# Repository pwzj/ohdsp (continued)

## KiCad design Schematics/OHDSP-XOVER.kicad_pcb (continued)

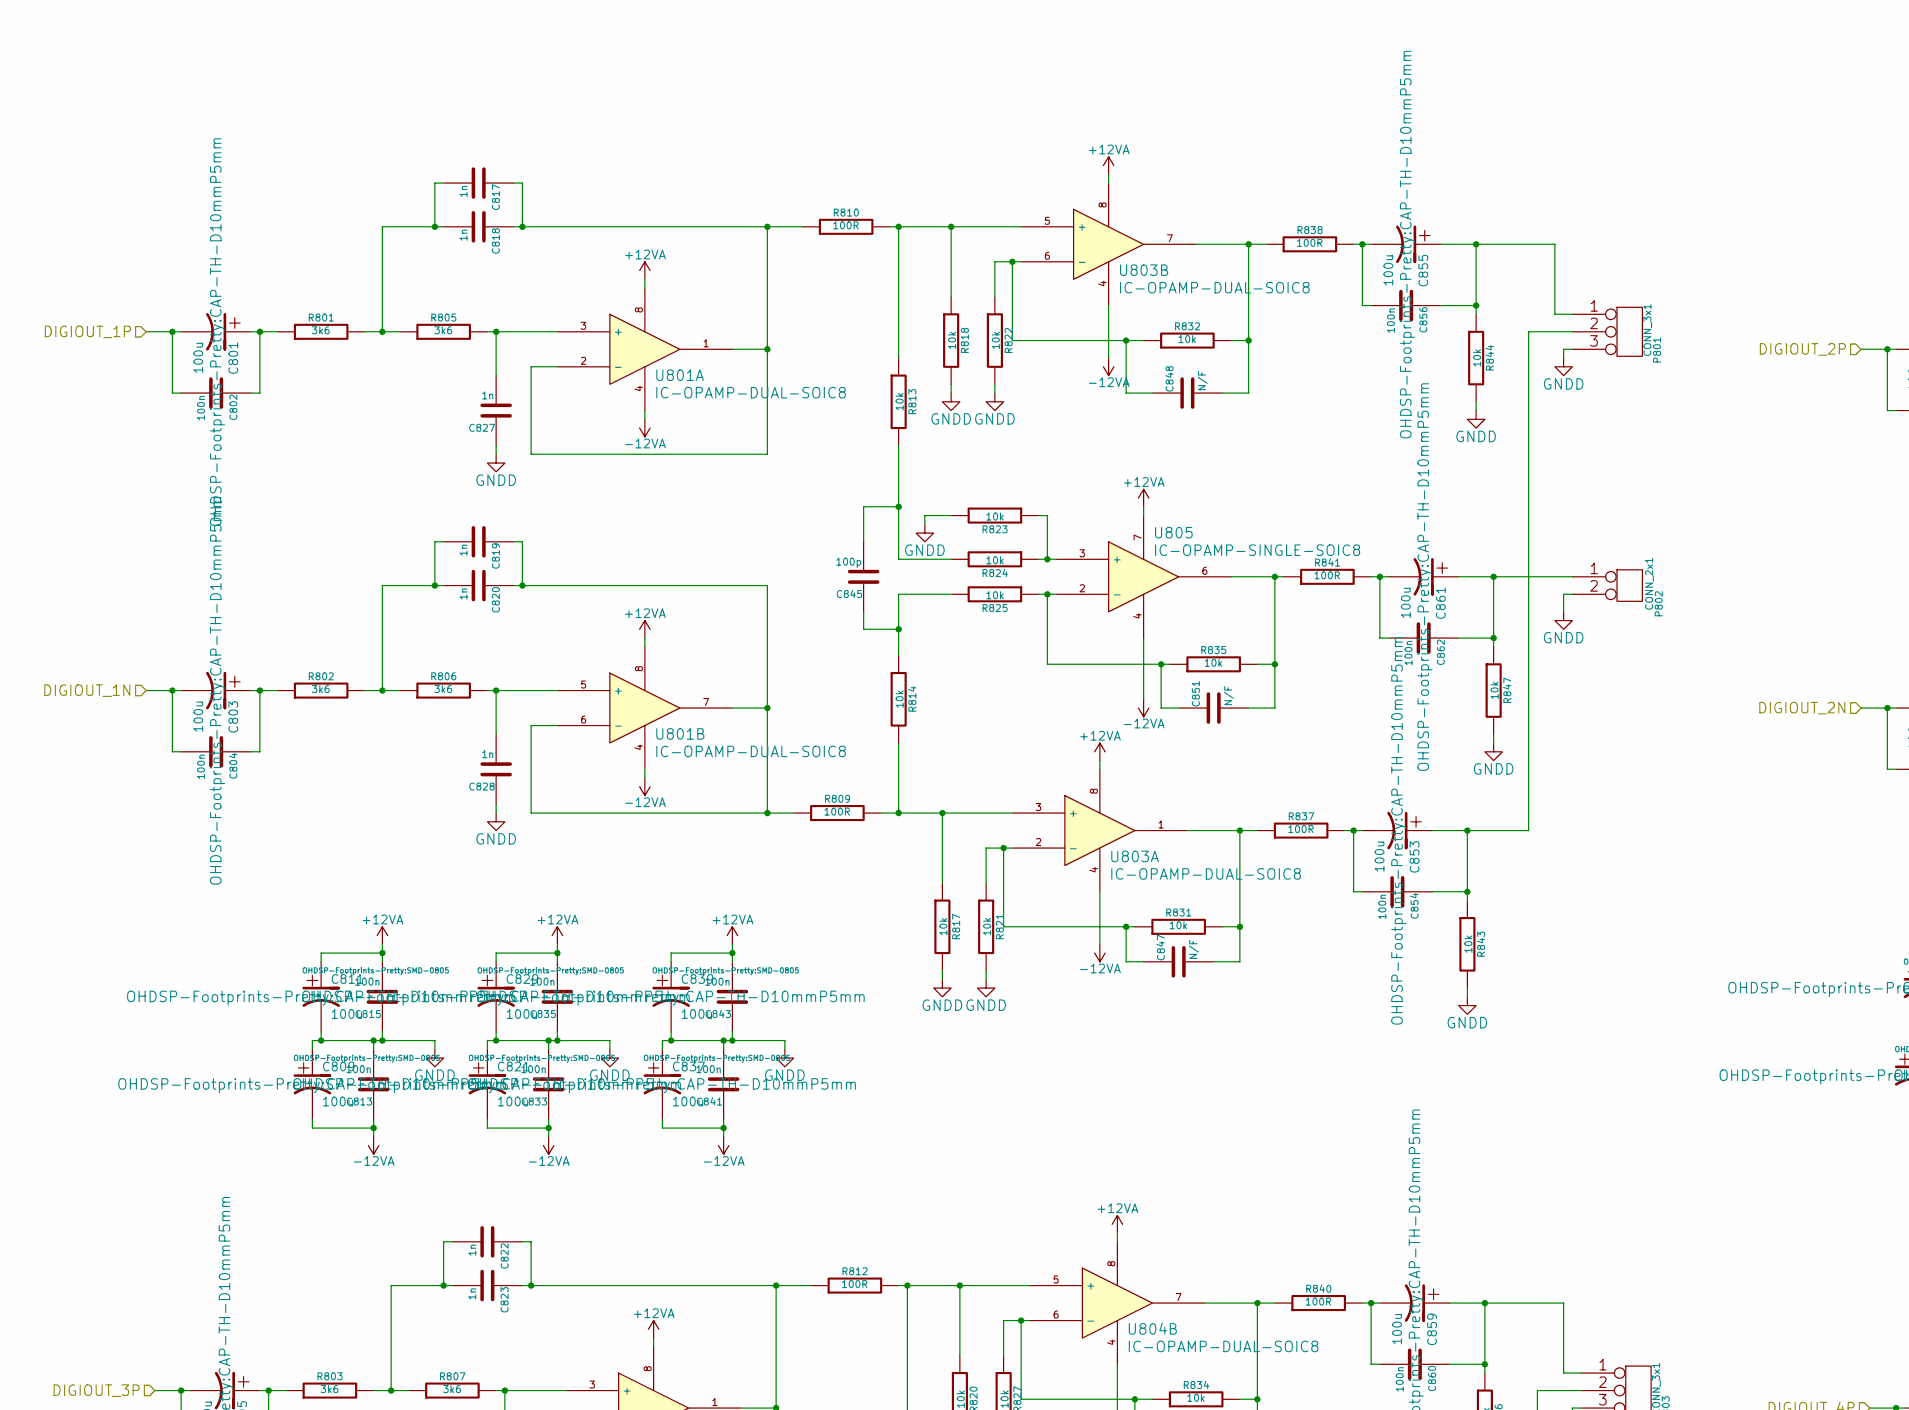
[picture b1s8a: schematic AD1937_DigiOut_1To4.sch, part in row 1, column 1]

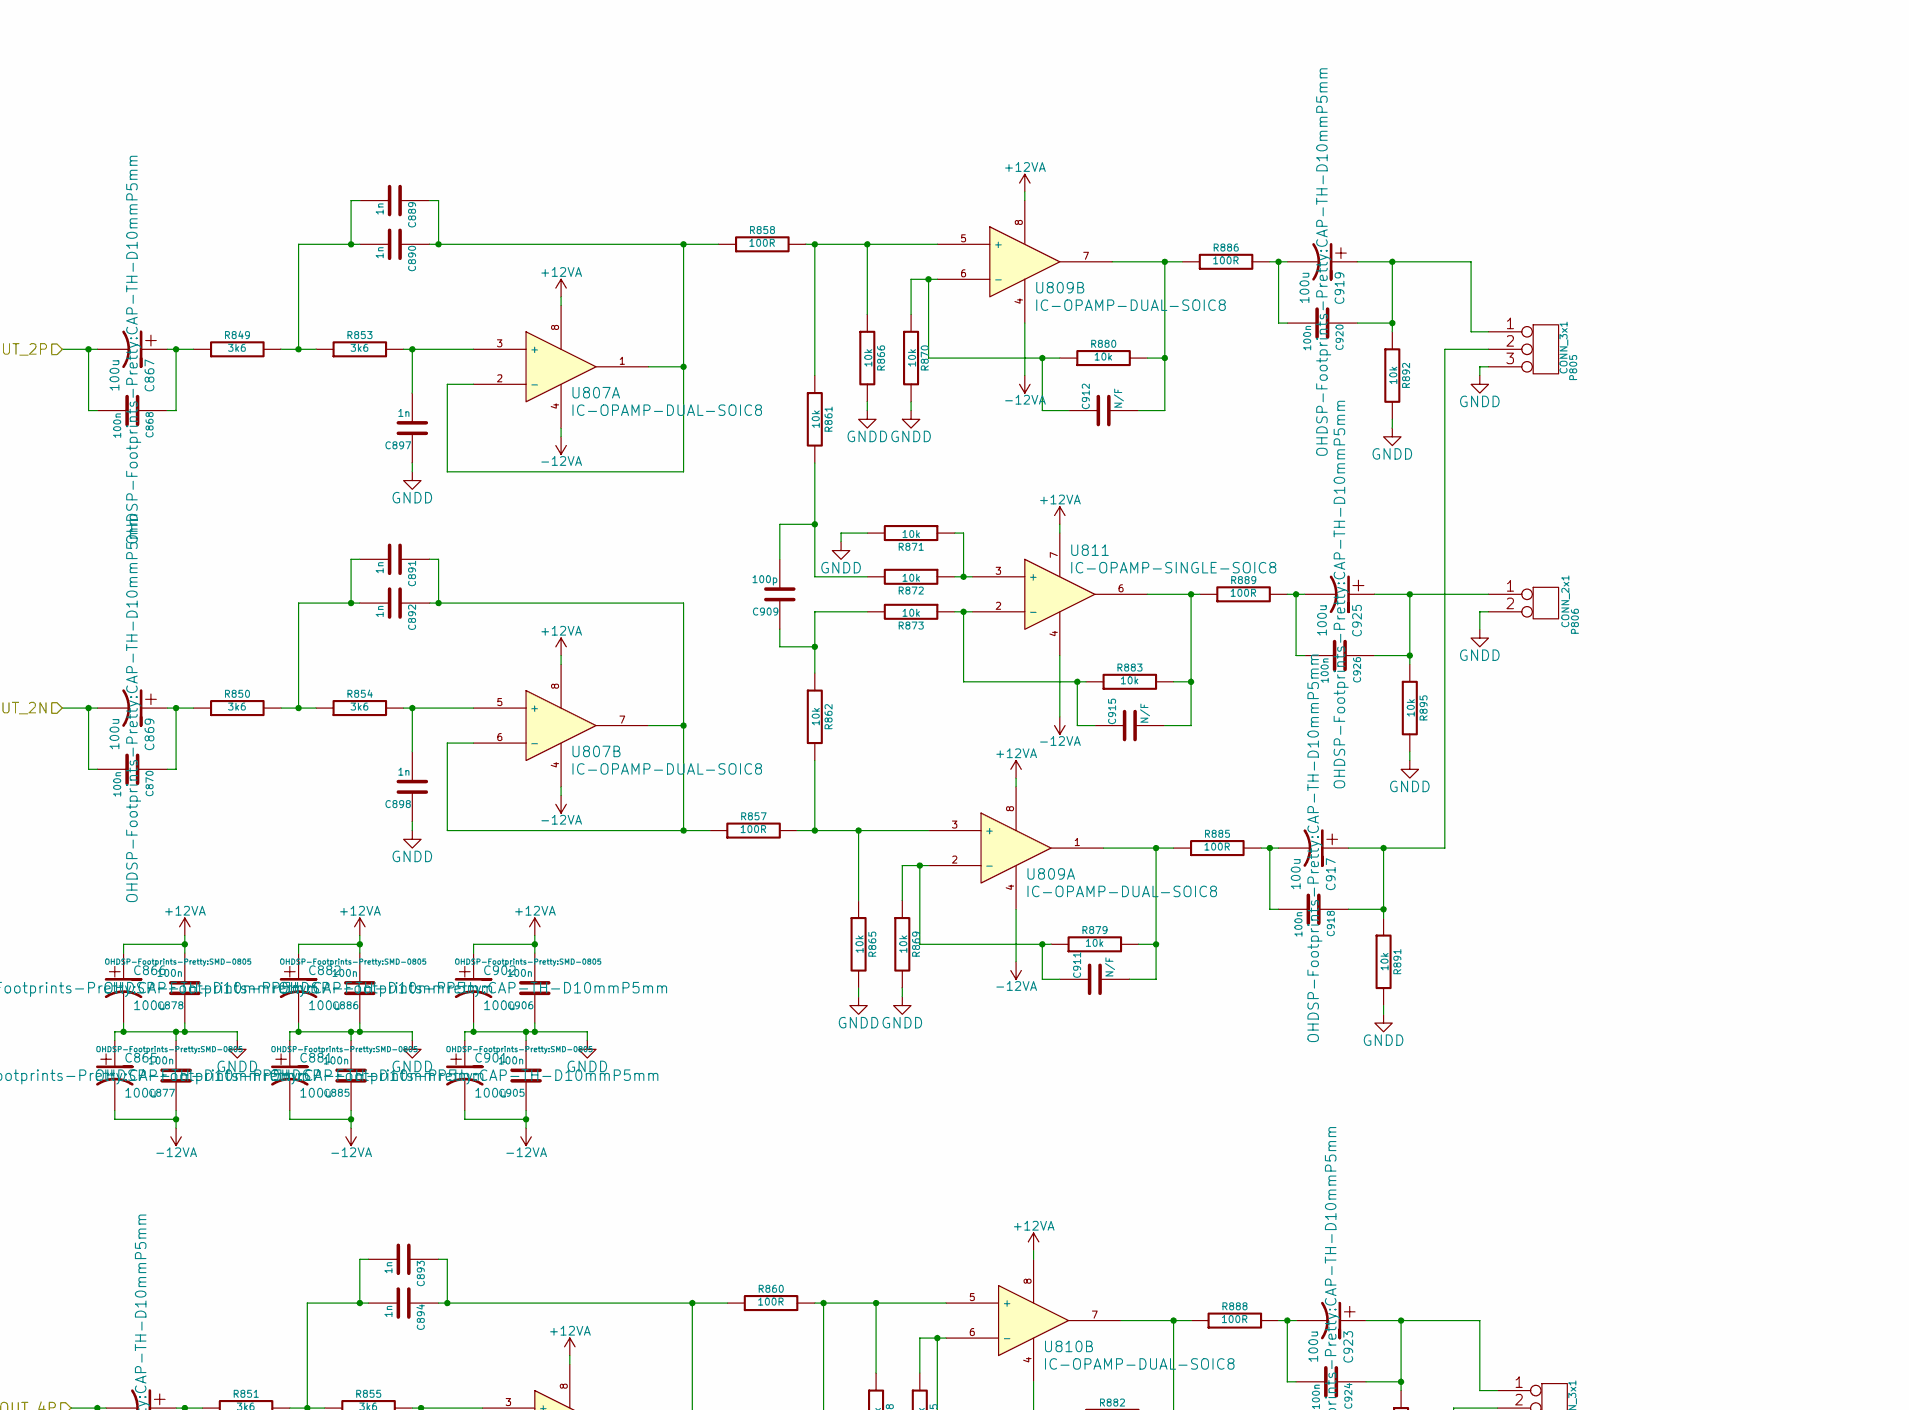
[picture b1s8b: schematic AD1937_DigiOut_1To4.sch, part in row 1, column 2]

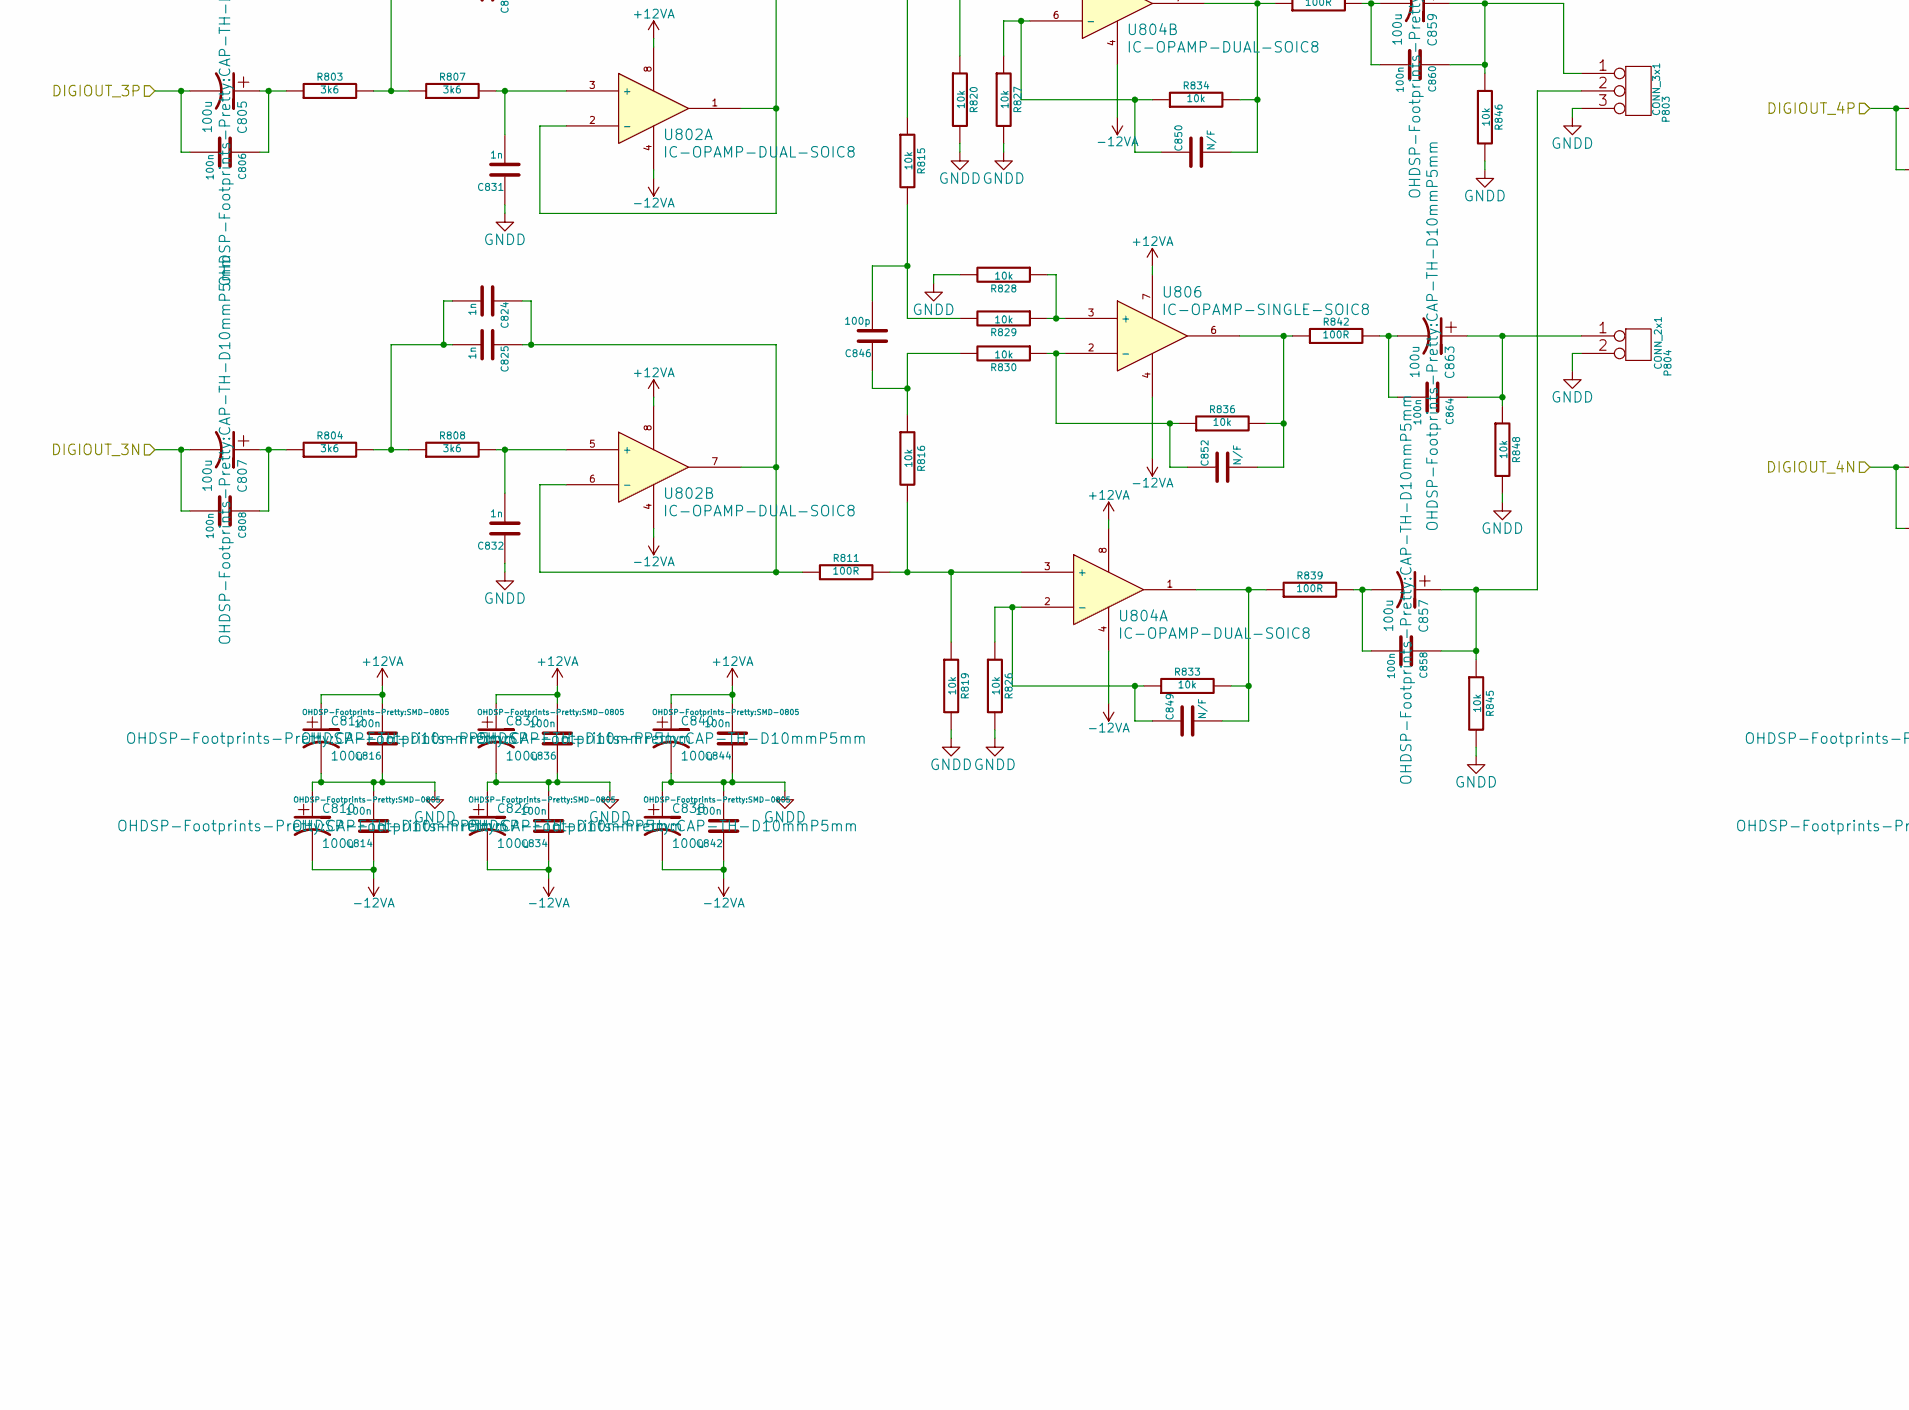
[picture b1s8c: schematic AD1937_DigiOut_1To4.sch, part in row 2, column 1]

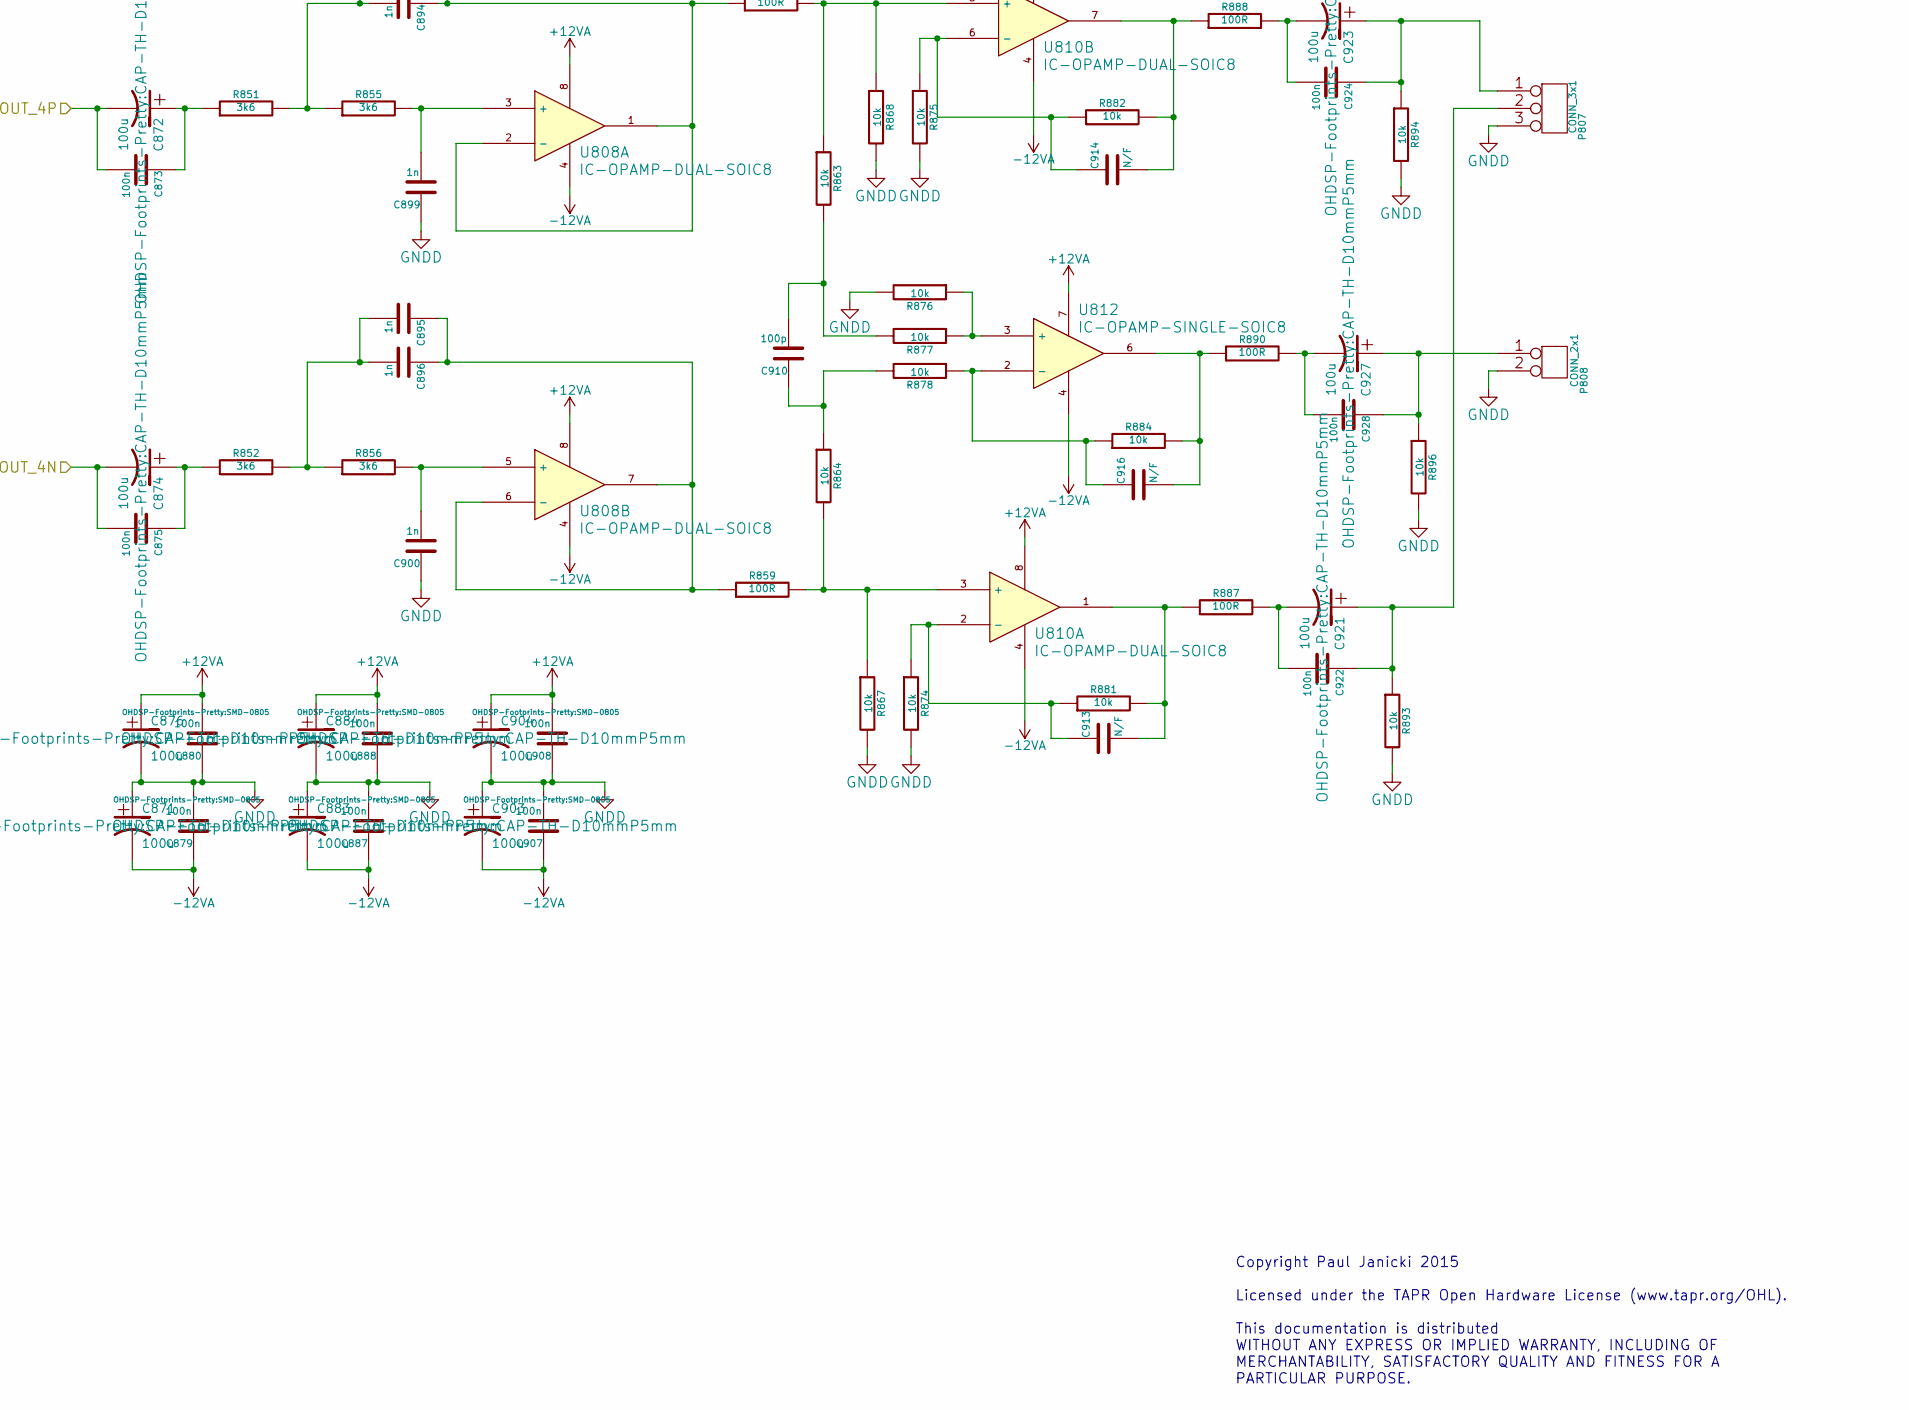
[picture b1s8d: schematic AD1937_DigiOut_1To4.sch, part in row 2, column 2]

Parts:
C801, C803, C805, C807, C809, C810, C811, C812, C821, C826, C829, C830, C837, C838, C839, C840, C853, C855, C857, C859, C861, C863, C865, C866, C867, C869, C871, C872, C874, C876, C881, C882, C883, C884, C901, C902, C903, C904, C917, C919, C921, C923, C925, C927: 100u; CAP-TH-D10mmP5mm
C802, C804, C806, C808, C854, C856, C858, C860, C862, C864, C868, C870, C873, C875, C918, C920, C922, C924, C926, C928: 100n; CAP_TH_5mm
C813, C814, C815, C816, C833, C834, C835, C836, C841, C842, C843, C844, C877, C878, C879, C880, C885, C886, C887, C888, C905, C906, C907, C908: 100n; SMD-0805
C817, C818, C819, C820, C822, C823, C824, C825, C827, C828, C831, C832, C889, C890, C891, C892, C893, C894, C895, C896, C897, C898, C899, C900: 1n; CAP_TH_5mm
C845, C846, C909, C910: 100p; CAP_TH_5mm
C847, C848, C849, C850, C851, C852, C911, C912, C913, C914, C915, C916: N/F; CAP_TH_5mm
P801, P803, P805, P807: CONN_3x1; CONN_SIL_3
P802, P804, P806, P808: CONN_2x1; CONN_SIL_2
R801, R802, R803, R804, R805, R806, R807, R808, R849, R850, R851, R852, R853, R854, R855, R856: 3k6; TH-RES-0W25
R809, R810, R811, R812, R837, R838, R839, R840, R841, R842, R857, R858, R859, R860, R885, R886, R887, R888, R889, R890: 100R; TH-RES-0W25
R813, R814, R815, R816, R817, R818, R819, R820, R821, R822, R823, R824, R825, R826, R827, R828, R829, R830, R831, R832, R833, R834, R835, R836, R843, R844, R845, R846, R847, R848, R861, R862, R863, R864, R865, R866, R867, R868, R869, R870, R871, R872, R873, R874, R875, R876, R877, R878, R879, R880, R881, R882, R883, R884, R891, R892, R893, R894, R895, R896: 10k; TH-RES-0W25
U801, U802, U803, U804, U807, U808, U809, U810: IC-OPAMP-DUAL-SOIC8; IC_DIP_8
U805, U806, U811, U812: IC-OPAMP-SINGLE-SOIC8; IC_DIP_8

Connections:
+12VA: C811.1, C812.1, C815.2, C816.2, C829.1, C830.1, C835.2, C836.2, C839.1, C840.1, C843.2, C844.2, C866.1, C876.1, C878.2, C880.2, C882.1, C884.1, C886.2, C888.2, C902.1, C904.1, C906.2, C908.2, U801.8, U802.8, U803.8, U804.8, U805.7, U806.7, U807.8, U808.8, U809.8, U810.8, U811.7, U812.7; also elsewhere on the board
-12VA: C809.2, C810.2, C813.1, C814.1, C821.2, C826.2, C833.1, C834.1, C837.2, C838.2, C841.1, C842.1, C865.2, C871.2, C877.1, C879.1, C881.2, C883.2, C885.1, C887.1, C901.2, C903.2, C905.1, C907.1, U801.4, U802.4, U803.4, U804.4, U805.4, U806.4, U807.4, U808.4, U809.4, U810.4, U811.4, U812.4; also elsewhere on the board
/AD1937 CODEC/DAC_OUT1_LN: C803.2, C804.2; also elsewhere on the board
/AD1937 CODEC/DAC_OUT1_LP: C801.2, C802.2; also elsewhere on the board
/AD1937 CODEC/DAC_OUT1_RN: C869.2, C870.2; also elsewhere on the board
/AD1937 CODEC/DAC_OUT1_RP: C867.2, C868.2; also elsewhere on the board
/AD1937 CODEC/DAC_OUT2_LN: C807.2, C808.2; also elsewhere on the board
/AD1937 CODEC/DAC_OUT2_LP: C805.2, C806.2; also elsewhere on the board
/AD1937 CODEC/DAC_OUT2_RN: C874.2, C875.2; also elsewhere on the board
/AD1937 CODEC/DAC_OUT2_RP: C872.2, C873.2; also elsewhere on the board
GNDD: C809.1, C810.1, C811.2, C812.2, C813.2, C814.2, C815.1, C816.1, C821.1, C826.1, C827.1, C828.1, C829.2, C830.2, C831.1, C832.1, C833.2, C834.2, C835.1, C836.1, C837.1, C838.1, C839.2, C840.2, C841.2, C842.2, C843.1, C844.1, C865.1, C866.2, C871.1, C876.2, C877.2, C878.1, C879.2, C880.1, C881.1, C882.2, C883.1, C884.2, C885.2, C886.1, C887.2, C888.1, C897.1, C898.1, C899.1, C900.1, C901.1, C902.2, C903.1, C904.2, C905.2, C906.1, C907.2, C908.1, P801.3, P802.2, P803.3, P804.2, P805.3, P806.2, P807.3, P808.2, R817.2, R818.2, R819.2, R820.2, R821.2, R822.2, R823.2, R826.2, R827.2, R828.2, R843.2, R844.2, R845.2, R846.2, R847.2, R848.2, R865.2, R866.2, R867.2, R868.2, R869.2, R870.2, R871.2, R874.2, R875.2, R876.2, R891.2, R892.2, R893.2, R894.2, R895.2, R896.2; also elsewhere on the board
unnamed: C801.1, C802.1, R801.1
unnamed: C803.1, C804.1, R802.1
unnamed: C805.1, C806.1, R803.1
unnamed: C807.1, C808.1, R804.1
unnamed: C817.1, C818.1, R810.1, U801.1, U801.2 (-)
unnamed: C817.2, C818.2, R801.2, R805.1
unnamed: C819.1, C820.1, R809.1, U801.6 (-), U801.7
unnamed: C819.2, C820.2, R802.2, R806.1
unnamed: C822.1, C823.1, R812.1, U802.1, U802.2 (-)
unnamed: C822.2, C823.2, R803.2, R807.1
unnamed: C824.1, C825.1, R811.1, U802.6 (-), U802.7
unnamed: C824.2, C825.2, R804.2, R808.1
unnamed: C827.2, R805.2, U801.3 (+)
unnamed: C828.2, R806.2, U801.5 (+)
unnamed: C831.2, R807.2, U802.3 (+)
unnamed: C832.2, R808.2, U802.5 (+)
unnamed: C845.1, R814.1, R825.2
unnamed: C845.2, R813.2, R824.2
unnamed: C846.1, R816.1, R830.2
unnamed: C846.2, R815.2, R829.2
unnamed: C847.1, R821.1, R831.1, U803.2 (-)
unnamed: C847.2, R831.2, R837.1, U803.1
unnamed: C848.1, R822.1, R832.1, U803.6 (-)
unnamed: C848.2, R832.2, R838.1, U803.7
unnamed: C849.1, R826.1, R833.1, U804.2 (-)
unnamed: C849.2, R833.2, R839.1, U804.1
unnamed: C850.1, R827.1, R834.1, U804.6 (-)
unnamed: C850.2, R834.2, R840.1, U804.7
unnamed: C851.1, R825.1, R835.1, U805.2 (-)
unnamed: C851.2, R835.2, R841.1, U805.6
unnamed: C852.1, R830.1, R836.1, U806.2 (-)
unnamed: C852.2, R836.2, R842.1, U806.6
unnamed: C853.1, C854.1, P801.2, R843.1
unnamed: C853.2, C854.2, R837.2
unnamed: C855.1, C856.1, P801.1, R844.1
unnamed: C855.2, C856.2, R838.2
unnamed: C857.1, C858.1, P803.2, R845.1
unnamed: C857.2, C858.2, R839.2
unnamed: C859.1, C860.1, P803.1, R846.1
unnamed: C859.2, C860.2, R840.2
unnamed: C861.1, C862.1, P802.1, R847.1
unnamed: C861.2, C862.2, R841.2
unnamed: C863.1, C864.1, P804.1, R848.1
unnamed: C863.2, C864.2, R842.2
unnamed: C867.1, C868.1, R849.1
unnamed: C869.1, C870.1, R850.1
unnamed: C872.1, C873.1, R851.1
unnamed: C874.1, C875.1, R852.1
unnamed: C889.1, C890.1, R858.1, U807.1, U807.2 (-)
unnamed: C889.2, C890.2, R849.2, R853.1
unnamed: C891.1, C892.1, R857.1, U807.6 (-), U807.7
unnamed: C891.2, C892.2, R850.2, R854.1
unnamed: C893.1, C894.1, R860.1, U808.1, U808.2 (-)
unnamed: C893.2, C894.2, R851.2, R855.1
unnamed: C895.1, C896.1, R859.1, U808.6 (-), U808.7
unnamed: C895.2, C896.2, R852.2, R856.1
unnamed: C897.2, R853.2, U807.3 (+)
unnamed: C898.2, R854.2, U807.5 (+)
unnamed: C899.2, R855.2, U808.3 (+)
unnamed: C900.2, R856.2, U808.5 (+)
unnamed: C909.1, R862.1, R873.2
unnamed: C909.2, R861.2, R872.2
unnamed: C910.1, R864.1, R878.2
unnamed: C910.2, R863.2, R877.2
unnamed: C911.1, R869.1, R879.1, U809.2 (-)
unnamed: C911.2, R879.2, R885.1, U809.1
unnamed: C912.1, R870.1, R880.1, U809.6 (-)
unnamed: C912.2, R880.2, R886.1, U809.7
unnamed: C913.1, R874.1, R881.1, U810.2 (-)
unnamed: C913.2, R881.2, R887.1, U810.1
unnamed: C914.1, R875.1, R882.1, U810.6 (-)
unnamed: C914.2, R882.2, R888.1, U810.7
unnamed: C915.1, R873.1, R883.1, U811.2 (-)
unnamed: C915.2, R883.2, R889.1, U811.6
unnamed: C916.1, R878.1, R884.1, U812.2 (-)
unnamed: C916.2, R884.2, R890.1, U812.6
unnamed: C917.1, C918.1, P805.2, R891.1
unnamed: C917.2, C918.2, R885.2
unnamed: C919.1, C920.1, P805.1, R892.1
unnamed: C919.2, C920.2, R886.2
unnamed: C921.1, C922.1, P807.2, R893.1
unnamed: C921.2, C922.2, R887.2
unnamed: C923.1, C924.1, P807.1, R894.1
unnamed: C923.2, C924.2, R888.2
unnamed: C925.1, C926.1, P806.1, R895.1
unnamed: C925.2, C926.2, R889.2
unnamed: C927.1, C928.1, P808.1, R896.1
unnamed: C927.2, C928.2, R890.2
unnamed: R809.2, R814.2, R817.1, U803.3 (+)
unnamed: R810.2, R813.1, R818.1, U803.5 (+)
unnamed: R811.2, R816.2, R819.1, U804.3 (+)
unnamed: R812.2, R815.1, R820.1, U804.5 (+)
unnamed: R823.1, R824.1, U805.3 (+)
unnamed: R828.1, R829.1, U806.3 (+)
unnamed: R857.2, R862.2, R865.1, U809.3 (+)
unnamed: R858.2, R861.1, R866.1, U809.5 (+)
unnamed: R859.2, R864.2, R867.1, U810.3 (+)
unnamed: R860.2, R863.1, R868.1, U810.5 (+)
unnamed: R871.1, R872.1, U811.3 (+)
unnamed: R876.1, R877.1, U812.3 (+)

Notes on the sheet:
Copyright Paul Janicki 2015 Licensed under the TAPR Open Hardware License (www.tapr.org/OHL). This documentation is distributed WITHOUT ANY EXPRESS OR IMPLIED WARRANTY, INCLUDING OF MERCHANTABILITY, SATISFACTORY QUALITY AND FITNESS FOR A PARTICULAR PURPOSE.

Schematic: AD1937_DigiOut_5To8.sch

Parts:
C929, C931, C933, C935, C937, C938, C939, C940, C949, C954, C957, C958, C965, C966, C967, C968, C981, C983, C985, C987, C989, C991, C993, C994, C995, C997, C999, C1000, C1002, C1004, C1009, C1010, C1011, C1012, C1029, C1030, C1031, C1032, C1045, C1047, C1049, C1051, C1053, C1055: 100u; CAP-TH-D10mmP5mm
C930, C932, C934, C936, C982, C984, C986, C988, C990, C992, C996, C998, C1001, C1003, C1046, C1048, C1050, C1052, C1054, C1056: 100n; CAP_TH_5mm
C941, C942, C943, C944, C961, C962, C963, C964, C969, C970, C971, C972, C1006, C1007, C1008, C1013, C1014, C1015, C1016, C1033, C1034, C1035, C1036: 100n; SMD-0805
C945, C946, C947, C948, C950, C951, C952, C953, C955, C956, C959, C960, C1017, C1018, C1019, C1020, C1021, C1022, C1023, C1024, C1025, C1026, C1027, C1028: 1n; CAP_TH_5mm
C973, C974, C1037, C1038: 100p; CAP_TH_5mm
C975, C976, C977, C978, C979, C980, C1039, C1040, C1041, C1042, C1043, C1044: N/F; CAP_TH_5mm
C1005: 100n; CAP-TH-D10mmP5mm
P901, P903, P905, P907: CONN_3x1; CONN_SIL_3
P902, P904, P906, P908: CONN_2x1; CONN_SIL_2
R901, R902, R903, R904, R905, R906, R907, R908, R949, R950, R951, R952, R953, R954, R955, R956: 3k6; TH-RES-0W25
R909, R910, R911, R912, R937, R938, R939, R940, R941, R942, R957, R958, R959, R960, R985, R986, R987, R988, R989, R990: 100R; TH-RES-0W25
R913, R914, R915, R916, R917, R918, R919, R920, R921, R922, R923, R924, R925, R926, R927, R928, R929, R930, R931, R932, R933, R934, R935, R936, R943, R944, R945, R946, R947, R948, R961, R962, R963, R964, R965, R966, R967, R968, R969, R970, R971, R972, R973, R974, R975, R976, R977, R978, R979, R980, R981, R982, R983, R984, R991, R992, R993, R994, R995, R996: 10k; TH-RES-0W25
U901, U902, U903, U904, U907, U908, U909, U910: IC-OPAMP-DUAL-SOIC8; IC_DIP_8
U905, U906, U911, U912: IC-OPAMP-SINGLE-SOIC8; IC_DIP_8

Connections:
+12VA: C939.1, C940.1, C943.2, C944.2, C957.1, C958.1, C963.2, C964.2, C967.1, C968.1, C971.2, C972.2, C994.1, C1004.1, C1006.2, C1008.2, C1010.1, C1012.1, C1014.2, C1016.2, C1030.1, C1032.1, C1034.2, C1036.2, U901.8, U902.8, U903.8, U904.8, U905.7, U906.7, U907.8, U908.8, U909.8, U910.8, U911.7, U912.7; also elsewhere on the board
-12VA: C937.2, C938.2, C941.1, C942.1, C949.2, C954.2, C961.1, C962.1, C965.2, C966.2, C969.1, C970.1, C993.2, C999.2, C1005.1, C1007.1, C1009.2, C1011.2, C1013.1, C1015.1, C1029.2, C1031.2, C1033.1, C1035.1, U901.4, U902.4, U903.4, U904.4, U905.4, U906.4, U907.4, U908.4, U909.4, U910.4, U911.4, U912.4; also elsewhere on the board
/AD1937 CODEC/DAC_OUT3_LN: C931.2, C932.2; also elsewhere on the board
/AD1937 CODEC/DAC_OUT3_LP: C929.2, C930.2; also elsewhere on the board
/AD1937 CODEC/DAC_OUT3_RN: C997.2, C998.2; also elsewhere on the board
/AD1937 CODEC/DAC_OUT3_RP: C995.2, C996.2; also elsewhere on the board
/AD1937 CODEC/DAC_OUT4_LN: C935.2, C936.2; also elsewhere on the board
/AD1937 CODEC/DAC_OUT4_LP: C933.2, C934.2; also elsewhere on the board
/AD1937 CODEC/DAC_OUT4_RN: C1002.2, C1003.2; also elsewhere on the board
/AD1937 CODEC/DAC_OUT4_RP: C1000.2, C1001.2; also elsewhere on the board
GNDD: C937.1, C938.1, C939.2, C940.2, C941.2, C942.2, C943.1, C944.1, C949.1, C954.1, C955.1, C956.1, C957.2, C958.2, C959.1, C960.1, C961.2, C962.2, C963.1, C964.1, C965.1, C966.1, C967.2, C968.2, C969.2, C970.2, C971.1, C972.1, C993.1, C994.2, C999.1, C1004.2, C1005.2, C1006.1, C1007.2, C1008.1, C1009.1, C1010.2, C1011.1, C1012.2, C1013.2, C1014.1, C1015.2, C1016.1, C1025.1, C1026.1, C1027.1, C1028.1, C1029.1, C1030.2, C1031.1, C1032.2, C1033.2, C1034.1, C1035.2, C1036.1, P901.3, P902.2, P903.3, P904.2, P905.3, P906.2, P907.3, P908.2, R917.2, R918.2, R919.2, R920.2, R921.2, R922.2, R923.2, R926.2, R927.2, R928.2, R943.2, R944.2, R945.2, R946.2, R947.2, R948.2, R965.2, R966.2, R967.2, R968.2, R969.2, R970.2, R971.2, R974.2, R975.2, R976.2, R991.2, R992.2, R993.2, R994.2, R995.2, R996.2; also elsewhere on the board
unnamed: C929.1, C930.1, R901.1
unnamed: C931.1, C932.1, R902.1
unnamed: C933.1, C934.1, R903.1
unnamed: C935.1, C936.1, R904.1
unnamed: C945.1, C946.1, R910.1, U901.1, U901.2 (-)
unnamed: C945.2, C946.2, R901.2, R905.1
unnamed: C947.1, C948.1, R909.1, U901.6 (-), U901.7
unnamed: C947.2, C948.2, R902.2, R906.1
unnamed: C950.1, C951.1, R912.1, U902.1, U902.2 (-)
unnamed: C950.2, C951.2, R903.2, R907.1
unnamed: C952.1, C953.1, R911.1, U902.6 (-), U902.7
unnamed: C952.2, C953.2, R904.2, R908.1
unnamed: C955.2, R905.2, U901.3 (+)
unnamed: C956.2, R906.2, U901.5 (+)
unnamed: C959.2, R907.2, U902.3 (+)
unnamed: C960.2, R908.2, U902.5 (+)
unnamed: C973.1, R914.1, R925.2
unnamed: C973.2, R913.2, R924.2
unnamed: C974.1, R916.1, R930.2
unnamed: C974.2, R915.2, R929.2
unnamed: C975.1, R921.1, R931.1, U903.2 (-)
unnamed: C975.2, R931.2, R937.1, U903.1
unnamed: C976.1, R922.1, R932.1, U903.6 (-)
unnamed: C976.2, R932.2, R938.1, U903.7
unnamed: C977.1, R926.1, R933.1, U904.2 (-)
unnamed: C977.2, R933.2, R939.1, U904.1
unnamed: C978.1, R927.1, R934.1, U904.6 (-)
unnamed: C978.2, R934.2, R940.1, U904.7
unnamed: C979.1, R925.1, R935.1, U905.2 (-)
unnamed: C979.2, R935.2, R941.1, U905.6
unnamed: C980.1, R930.1, R936.1, U906.2 (-)
unnamed: C980.2, R936.2, R942.1, U906.6
unnamed: C981.1, C982.1, P901.2, R943.1
unnamed: C981.2, C982.2, R937.2
unnamed: C983.1, C984.1, P901.1, R944.1
unnamed: C983.2, C984.2, R938.2
unnamed: C985.1, C986.1, P903.2, R945.1
unnamed: C985.2, C986.2, R939.2
unnamed: C987.1, C988.1, P903.1, R946.1
unnamed: C987.2, C988.2, R940.2
unnamed: C989.1, C990.1, P902.1, R947.1
unnamed: C989.2, C990.2, R941.2
unnamed: C991.1, C992.1, P904.1, R948.1
unnamed: C991.2, C992.2, R942.2
unnamed: C995.1, C996.1, R949.1
unnamed: C997.1, C998.1, R950.1
unnamed: C1000.1, C1001.1, R951.1
unnamed: C1002.1, C1003.1, R952.1
unnamed: C1017.1, C1018.1, R958.1, U907.1, U907.2 (-)
unnamed: C1017.2, C1018.2, R949.2, R953.1
unnamed: C1019.1, C1020.1, R957.1, U907.6 (-), U907.7
unnamed: C1019.2, C1020.2, R950.2, R954.1
unnamed: C1021.1, C1022.1, R960.1, U908.1, U908.2 (-)
unnamed: C1021.2, C1022.2, R951.2, R955.1
unnamed: C1023.1, C1024.1, R959.1, U908.6 (-), U908.7
unnamed: C1023.2, C1024.2, R952.2, R956.1
unnamed: C1025.2, R953.2, U907.3 (+)
unnamed: C1026.2, R954.2, U907.5 (+)
unnamed: C1027.2, R955.2, U908.3 (+)
unnamed: C1028.2, R956.2, U908.5 (+)
unnamed: C1037.1, R962.1, R973.2
unnamed: C1037.2, R961.2, R972.2
unnamed: C1038.1, R964.1, R978.2
unnamed: C1038.2, R963.2, R977.2
unnamed: C1039.1, R969.1, R979.1, U909.2 (-)
unnamed: C1039.2, R979.2, R985.1, U909.1
unnamed: C1040.1, R970.1, R980.1, U909.6 (-)
unnamed: C1040.2, R980.2, R986.1, U909.7
unnamed: C1041.1, R974.1, R981.1, U910.2 (-)
unnamed: C1041.2, R981.2, R987.1, U910.1
unnamed: C1042.1, R975.1, R982.1, U910.6 (-)
unnamed: C1042.2, R982.2, R988.1, U910.7
unnamed: C1043.1, R973.1, R983.1, U911.2 (-)
unnamed: C1043.2, R983.2, R989.1, U911.6
unnamed: C1044.1, R978.1, R984.1, U912.2 (-)
unnamed: C1044.2, R984.2, R990.1, U912.6
unnamed: C1045.1, C1046.1, P905.2, R991.1
unnamed: C1045.2, C1046.2, R985.2
unnamed: C1047.1, C1048.1, P905.1, R992.1
unnamed: C1047.2, C1048.2, R986.2
unnamed: C1049.1, C1050.1, P907.2, R993.1
unnamed: C1049.2, C1050.2, R987.2
unnamed: C1051.1, C1052.1, P907.1, R994.1
unnamed: C1051.2, C1052.2, R988.2
unnamed: C1053.1, C1054.1, P906.1, R995.1
unnamed: C1053.2, C1054.2, R989.2
unnamed: C1055.1, C1056.1, P908.1, R996.1
unnamed: C1055.2, C1056.2, R990.2
unnamed: R909.2, R914.2, R917.1, U903.3 (+)
unnamed: R910.2, R913.1, R918.1, U903.5 (+)
unnamed: R911.2, R916.2, R919.1, U904.3 (+)
unnamed: R912.2, R915.1, R920.1, U904.5 (+)
unnamed: R923.1, R924.1, U905.3 (+)
unnamed: R928.1, R929.1, U906.3 (+)
unnamed: R957.2, R962.2, R965.1, U909.3 (+)
unnamed: R958.2, R961.1, R966.1, U909.5 (+)
unnamed: R959.2, R964.2, R967.1, U910.3 (+)
unnamed: R960.2, R963.1, R968.1, U910.5 (+)
unnamed: R971.1, R972.1, U911.3 (+)
unnamed: R976.1, R977.1, U912.3 (+)

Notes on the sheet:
Copyright Paul Janicki 2015 Licensed under the TAPR Open Hardware License (www.tapr.org/OHL). This documentation is distributed WITHOUT ANY EXPRESS OR IMPLIED WARRANTY, INCLUDING OF MERCHANTABILITY, SATISFACTORY QUALITY AND FITNESS FOR A PARTICULAR PURPOSE.

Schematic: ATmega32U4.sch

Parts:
C1057, C1064, C1065: 220u; CAP-TH-D6.3mmP2.5mm
C1058, C1066, C1067: 22u; SMD-0805
C1059, C1061, C1063, C1068, C1069, C1071, C1073, C1079, C1080: 100n; SMD-0805
C1060, C1062, C1070, C1072, C1077: 1u; SMD-0805
C1074, C1075: 22p; SMD-0805
C1076: 1n; SMD-0805
C1078: 10u; SMD-0805
L1001, L1002: 600R@100MHz; SMD-0805
P1001: CONN_02X05; CONN_DIL_2X5_BOX
P1002: CONN_5x1; CONN_SIL_5
R1001, R1002, R1003, R1004, R1007, R1008: 0R; SMD-0805
R1005, R1006: 22R; SMD-0805
R1009, R1010, R1011: 27R; SMD-0805
R1012: 10k; SMD-0805
R1013, R1014: 2k2; SMD-0805
U1001: IC-uC-ATmega32U4; IC-LQFP-44-10x10
X1001: 8MHz; XTAL_HC49_TH

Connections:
/ATmega32U4/I2C_SCL: R1007.1, R1014.2
/ATmega32U4/I2C_SDA: R1008.1, R1013.2
/ATmega32U4/MEGA_AVCC: C1064.1, C1066.1, C1068.1, C1070.1, C1071.1, C1072.1, C1073.1, L1002.2, U1001.24 (AVCC), U1001.44 (AVCC)
/ATmega32U4/MEGA_RESET: P1001.8, R1011.1
/ATmega32U4/MEGA_VCC: C1057.1, C1058.1, C1059.1, C1060.1, C1061.1, C1062.1, C1063.1, C1077.1, L1001.2, P1001.4, R1012.1, U1001.6 (UCap), U1001.14 (VCC), U1001.34 (VCC)
/ATmega32U4/SELFBOOT_EN: R1009.1
/ATmega32U4/SELFBOOT_WP: R1010.1
/ATmega32U4/TCK: P1001.1, R1001.2
/ATmega32U4/TDI: P1001.9, R1004.2
/ATmega32U4/TDO: P1001.3, R1002.2
/ATmega32U4/TMS: P1001.5, R1003.2
/ATmega32U4/USB_DN: P1002.2, R1005.1
/ATmega32U4/USB_DP: P1002.3, R1006.1
/ATmega32U4/USB_VBUS: C1078.1, C1079.1, P1002.1, U1001.7 (VBus)
/ATmega32U4/XTAL1: C1075.1, U1001.17 (XTAL1), X1001.2
/ATmega32U4/XTAL2: C1074.1, U1001.16 (XTAL2), X1001.1
GNDD: C1057.2, C1058.2, C1059.2, C1060.2, C1061.2, C1062.2, C1063.2, C1064.2, C1065.2, C1066.2, C1067.2, C1068.2, C1069.2, C1070.2, C1071.2, C1072.2, C1073.2, C1074.2, C1075.2, C1076.2, C1077.2, C1078.2, C1079.2, C1080.2, P1001.2, P1001.10, P1002.5, U1001.5 (UGnd), U1001.15 (GND), U1001.23 (GND), U1001.35 (GND), U1001.43 (GND); also elsewhere on the board
unnamed: C1065.1, C1067.1, C1069.1, U1001.42 (AREF)
unnamed: C1076.1, R1011.2, R1012.2, U1001.13 (~RESET~)
unnamed: R1001.1, U1001.39 (PF4(ADC4/TCK))
unnamed: R1002.1, U1001.37 (PF6(ADC6/TDO))
unnamed: R1003.1, U1001.38 (PF5(ADC5/TMS))
unnamed: R1004.1, U1001.36 (PF7(ADC7/TDI))
unnamed: R1005.2, U1001.3 (DN)
unnamed: R1007.2, U1001.18 (PD0(OC0B/SCL/INT0))
unnamed: R1008.2, U1001.19 (PD1(SDA/INT1))
unnamed: R1009.2, U1001.26 (PD6(T1/~OC4D~/ADC9))
unnamed: R1010.2, U1001.27 (PD7(T0/0C4D/ADC10))
VMEM: L1001.1, L1002.1; also elsewhere on the board
VPP: C1080.1, R1013.1, R1014.1; also elsewhere on the board

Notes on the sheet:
I2C Pull-ups
I2C
I2C Interface
Used for external control
Copyright Paul Janicki 2015 Licensed under the TAPR Open Hardware License (www.tapr.org/OHL). This documentation is distributed WITHOUT ANY EXPRESS OR IMPLIED WARRANTY, INCLUDING OF MERCHANTABILITY, SATISFACTORY QUALITY AND FITNESS FOR A PARTICULAR PURPOSE.
JTAG

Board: 4 copper layers, 1016 parts (0 on the bottom side), 464 nets, no tracks yet.
